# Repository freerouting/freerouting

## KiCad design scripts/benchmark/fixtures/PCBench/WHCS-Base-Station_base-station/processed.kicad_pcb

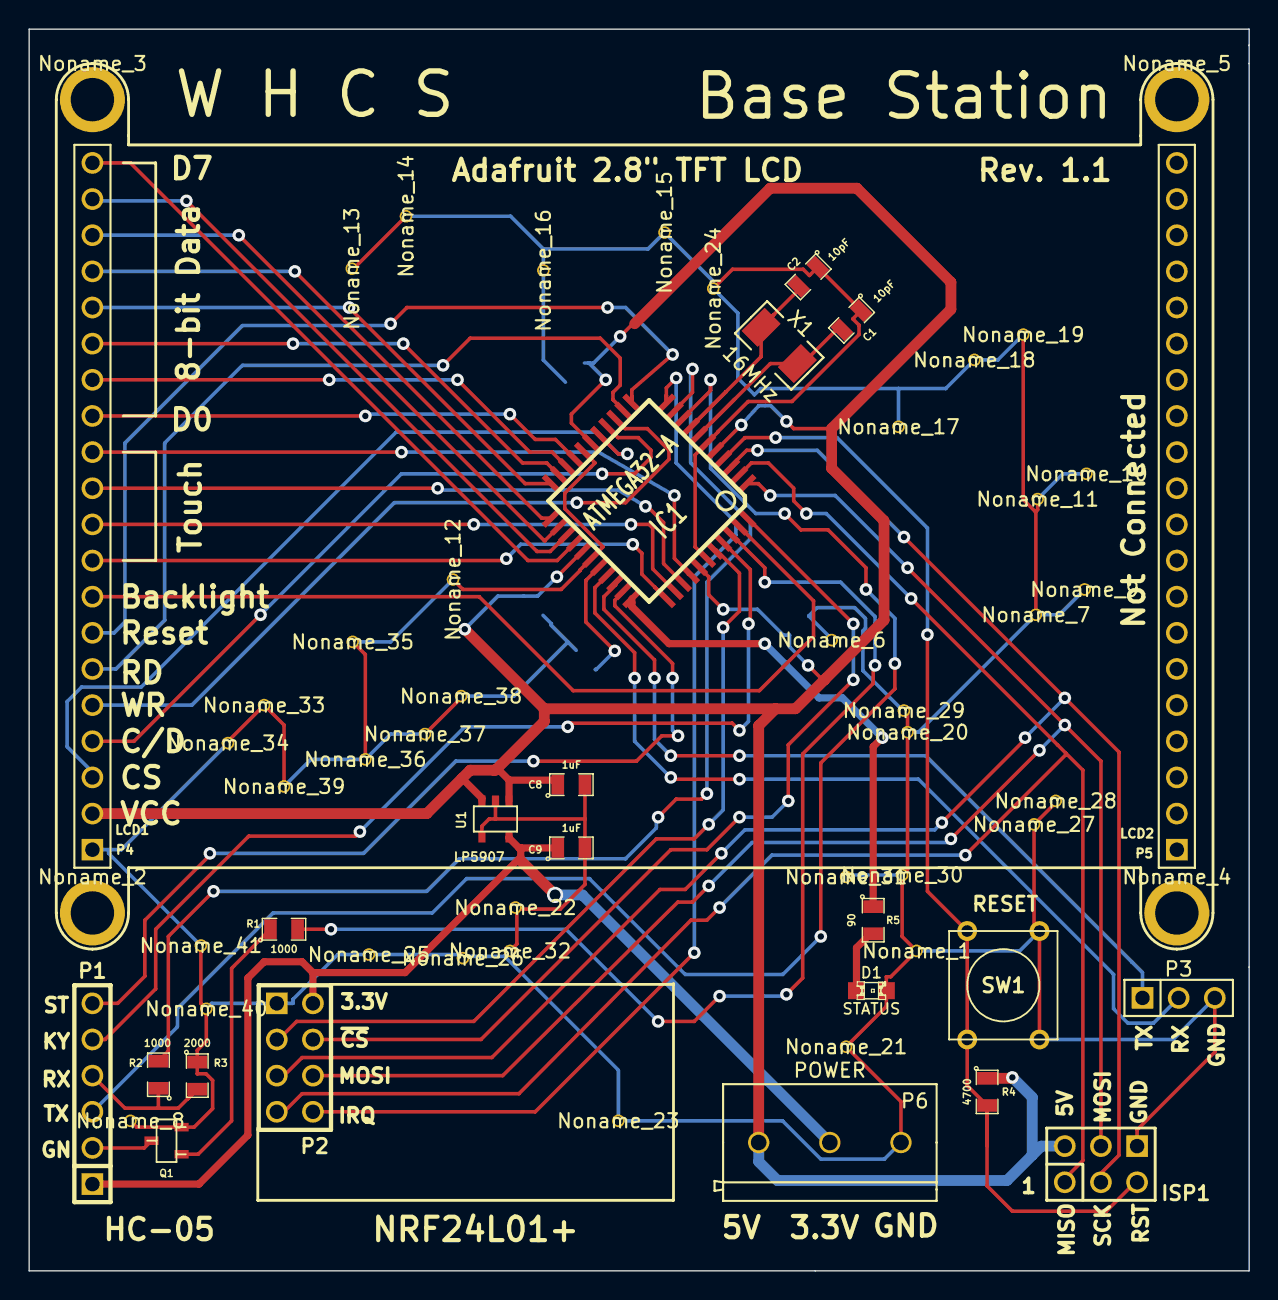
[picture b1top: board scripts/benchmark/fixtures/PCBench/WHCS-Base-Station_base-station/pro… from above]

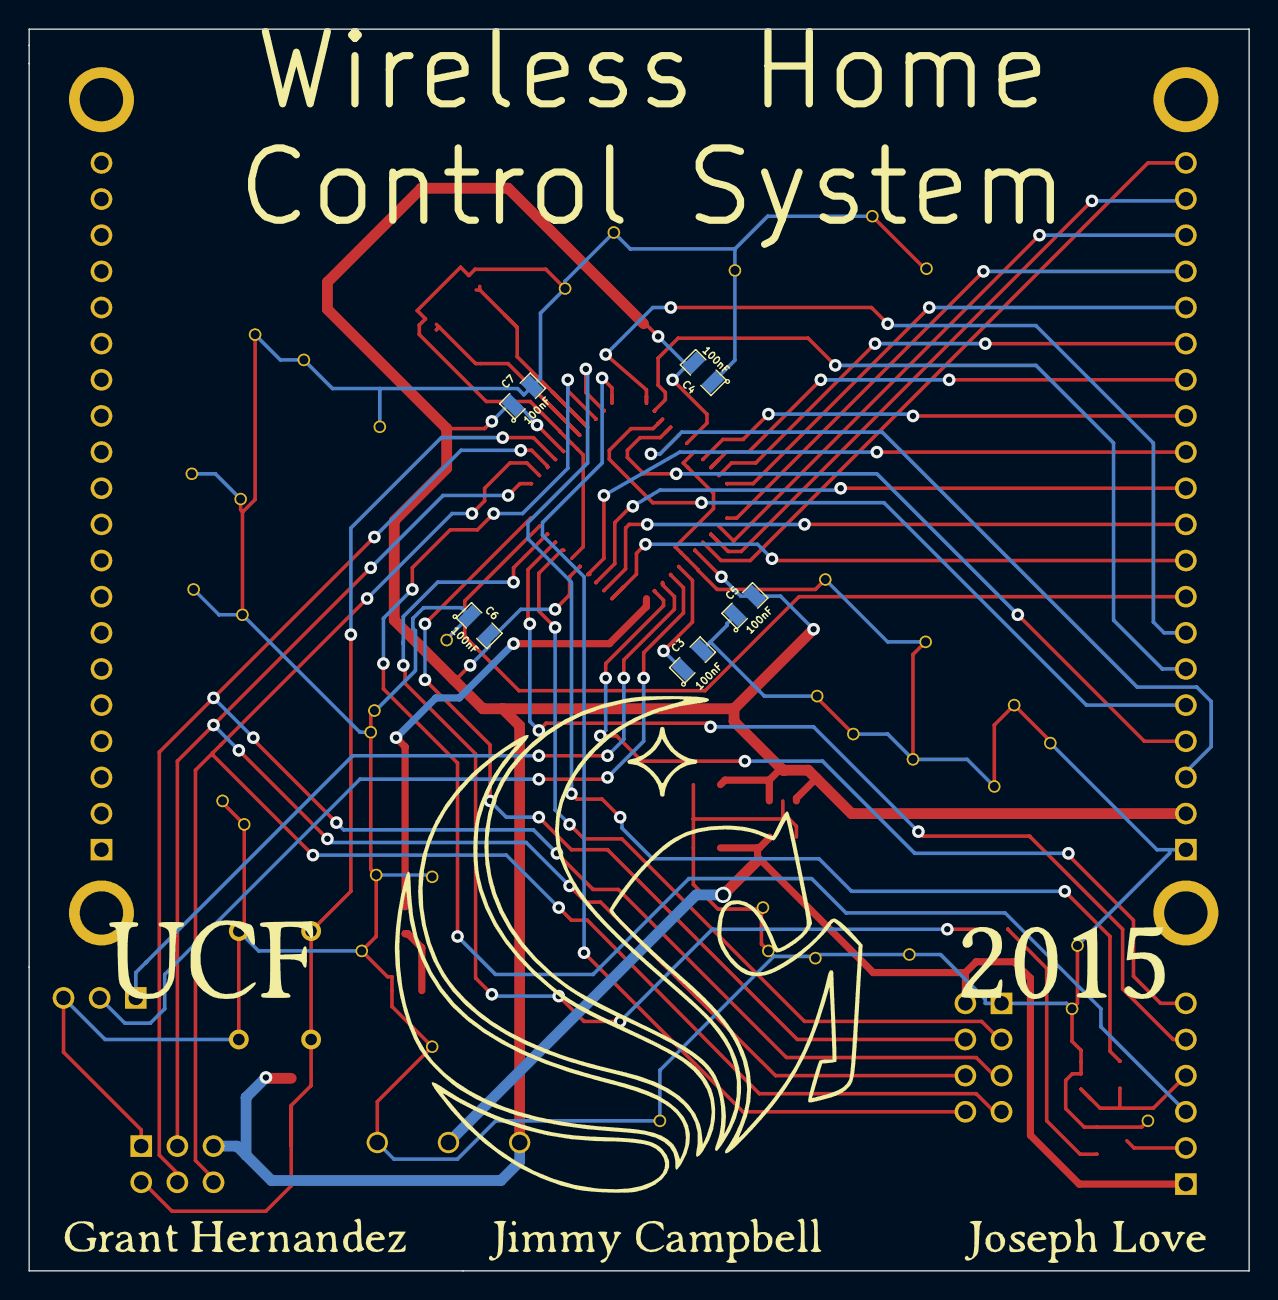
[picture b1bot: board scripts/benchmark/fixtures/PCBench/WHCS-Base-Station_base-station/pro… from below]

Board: 2 copper layers, 85.7 x 87.2 mm, 68 parts (5 on the bottom side), 43 nets.

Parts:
C1, C2: 10pF; SM0805
C3, C4, C5, C6, C7: 100nF; SM0805
C8, C9: 1uF; SM0805
D1: STATUS; LED-0805
IC1: ATMEGA32-A; TQFP44
ISP1: ISP; pin_array_3x2
Noname_1, Noname_6, Noname_7, Noname_8, Noname_9, Noname_10, Noname_11, Noname_12, Noname_13, Noname_14, Noname_15, Noname_16, Noname_17, Noname_18, Noname_19, Noname_20, Noname_21, Noname_22, Noname_23, Noname_24, Noname_25, Noname_26, Noname_27, Noname_28, Noname_29, Noname_30, Noname_31, Noname_32, Noname_33, Noname_34, Noname_35, Noname_36, Noname_37, Noname_38, Noname_39, Noname_40, Noname_41: gnd-via
Noname_2, Noname_3, Noname_4, Noname_5: adafruit-tft-mount
P1: HC-05; PIN_ARRAY-6X1
P2: NRF24L01+; pin_array_4x2
P3: SERIAL; PIN_ARRAY_3X1
P4: LCD1; PIN_ARRAY_20X1
P5: LCD2; PIN_ARRAY_20X1
P6: POWER; terminal-282836-3
Q1: BTEN; sot23
R1, R2: 1000; SM0805
R3: 2000; SM0805
R4: 4700; SM0805
R5: 90; SM0805
SW1: RESET; SW_PUSH_SMALL
U1: LP5907; SOT23-5
X1: 16MHz; 2-SMD

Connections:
/3V3: C9.1, P1.1, P2.2, P6.2, U1.5
/BTEN: IC1.42, R1.2
/CD: IC1.15, P4.4
/CE: IC1.40, P2.3
/CSN: IC1.44, P2.4
/D0: IC1.19, P4.13
/D1: IC1.20, P4.14
/D2: IC1.21, P4.15
/D3: IC1.22, P4.16
/D4: IC1.23, P4.17
/D5: IC1.24, P4.18
/D6: IC1.25, P4.19
/D7: IC1.26, P4.20
/HC_GND: P1.2, Q1.2
/IRQ: IC1.11, P2.8
/KEY: IC1.41, P1.5
/LCS: IC1.16, P4.3
/LITE: IC1.43, P4.8
/LRST: IC1.12, P4.7
/MISO: IC1.2, ISP1.1, P2.7
/MOSI: IC1.1, ISP1.4, P2.6
/PA4: IC1.33, R5.1
/RD: IC1.13, P4.6
/RST: IC1.4, ISP1.5, R4.2, SW1.1
/RX: IC1.9, P1.3
/RX_SOFT: IC1.30, P3.2
/SCK: IC1.3, ISP1.3, P2.5
/STATUS: IC1.32, P1.6
/TX: IC1.10, R2.2
/TX_SOFT: IC1.31, P3.1
/VCC: C4.2, C5.2, C6.2, C7.1, C8.1, IC1.5, IC1.17, IC1.27, IC1.38, ISP1.2, P4.2, P6.1, R4.1, U1.1, U1.3
/WR: IC1.14, P4.5
/X+: IC1.34, P4.9
/X-: IC1.36, P4.11
/Y+: IC1.35, P4.10
/Y-: IC1.37, P4.12
GND: C1.1, C2.1, C3.2, C4.1, C5.1, C6.1, C7.2, C8.2, C9.2, D1.2, IC1.6, IC1.18, IC1.28, IC1.39, ISP1.6, P2.1, P3.3, P4.1, P6.3, Q1.3, R3.1, SW1.2, U1.2, U1.4
unnamed: C1.2, IC1.7, X1.2
unnamed: C2.2, IC1.8, X1.1
unnamed: Q1.1, R1.1
unnamed: P1.4, R2.1, R3.2
unnamed: D1.1, R5.2
unnamed: C3.1, IC1.29

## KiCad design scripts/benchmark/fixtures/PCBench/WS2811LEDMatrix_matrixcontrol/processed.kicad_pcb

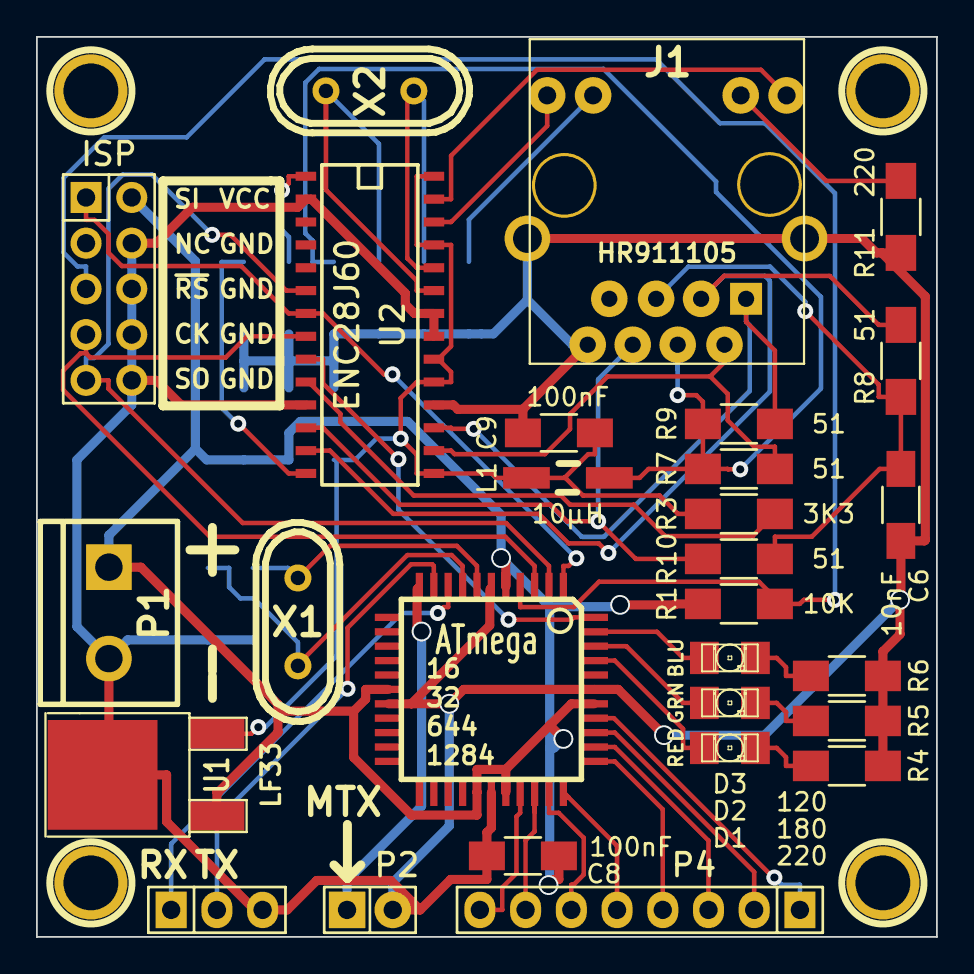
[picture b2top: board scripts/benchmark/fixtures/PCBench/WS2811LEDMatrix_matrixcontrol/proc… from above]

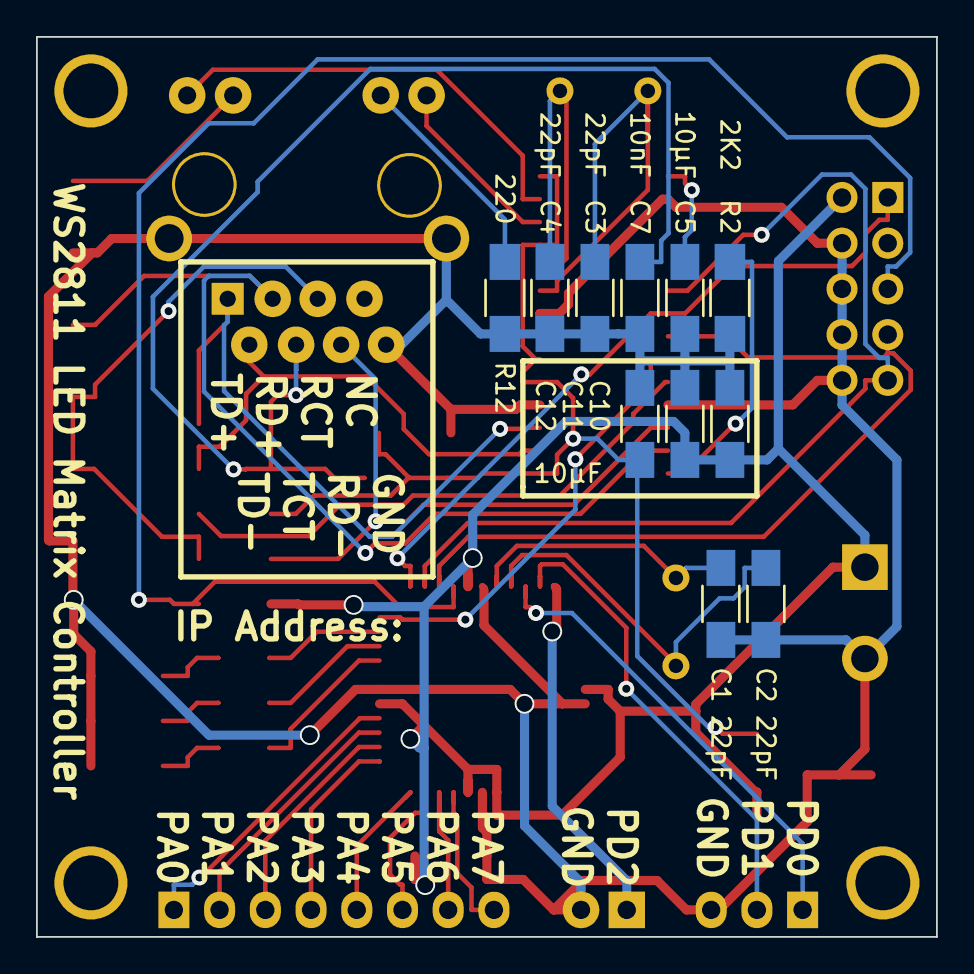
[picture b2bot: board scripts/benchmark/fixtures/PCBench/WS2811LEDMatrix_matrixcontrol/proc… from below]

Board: 2 copper layers, 50.0 x 50.0 mm, 43 parts (11 on the bottom side), 42 nets.

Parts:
C1, C2, C3, C4: 22pF; C_1206_HandSoldering
C5, C10, C11, C12: 10µF; C_1206_HandSoldering
C6, C7: 10nF; C_1206_HandSoldering
C8, C9: 100nF; C_1206_HandSoldering
D1: RED; LED-1206
D2: GRN; LED-1206
D3: BLU; LED-1206
IC1: ATmega; TQFP-44
ISP: ISP; Pin_Header_Straight_2x05
J1: HR911105; HR911105_RJ45
L1: 10µH; Choke_SMD_1206_Handsoldering
MOUNT1, MOUNT2, MOUNT3, MOUNT4: 1pin
P1: POWER_IN; bornier2
P2: MATRIX DATA; Pin_Header_Straight_1x02
P3: SERIAL; Pin_Header_Straight_1x03
P4: CONN_01X08; Pin_Header_Straight_1x08
R1: 10K; R_1206_HandSoldering
R2: 2K2; R_1206_HandSoldering
R3: 3K3; R_1206_HandSoldering
R4, R11, R12: 220; R_1206_HandSoldering
R5: 180; R_1206_HandSoldering
R6: 120; R_1206_HandSoldering
R7, R8, R9, R10: 51; R_1206_HandSoldering
U1: LF33; DPAK-2
U2: ENC28J60; SOIC-28
X1: 16MHz; Crystal_HC49-U_Vertical
X2: 25MHz; Crystal_HC49-U_Vertical

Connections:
+5V: C8.1, C10.1, C11.1, IC1.5, IC1.17, IC1.27, IC1.29, IC1.38, ISP.2, P1.1, R1.1, U1.1
/MISO: IC1.2, ISP.9, U2.6
/MOSI: IC1.1, ISP.1, U2.7
/MTX_DAT: IC1.11, P2.1
/RXD: IC1.9, P3.1
/SCK: IC1.3, ISP.7, U2.8
/STATLED1: D1.1, IC1.41
/STATLED2: D2.1, IC1.42
/STATLED3: D3.1, IC1.43
/TXD: IC1.10, P3.2
/~RESET: IC1.4, ISP.5, R1.2
GND: C1.2, C2.2, C3.2, C4.2, C5.2, C6.2, C7.2, C8.2, C9.2, C10.2, C11.2, C12.2, IC1.6, IC1.18, IC1.28, IC1.39, ISP.4, ISP.6, ISP.8, ISP.10, J1.0, J1.8, P1.2, P2.2, P3.3, R2.2, R4.1, R5.1, R6.1, R11.2, R12.2, U1.2, U2.2, U2.11, U2.18, U2.21, U2.22
unnamed: C1.1, IC1.7, X1.1
unnamed: C2.1, IC1.8, X1.2
unnamed: C3.1, U2.23, X2.1
unnamed: C4.1, U2.24, X2.2
unnamed: C5.1, U2.1
unnamed: C6.1, J1.5, R8.2, R10.2
unnamed: C7.1, J1.4, L1.2, R7.1, R9.1
unnamed: C9.1, C12.1, L1.1, R3.1, U1.3, U2.15, U2.19, U2.20, U2.25, U2.28
unnamed: D1.2, R4.2
unnamed: D2.2, R5.2
unnamed: D3.2, R6.2
unnamed: IC1.30, P4.8
unnamed: IC1.31, P4.7
unnamed: IC1.32, P4.6
unnamed: IC1.33, P4.5
unnamed: IC1.34, P4.4
unnamed: IC1.35, P4.3
unnamed: IC1.36, P4.2
unnamed: IC1.37, P4.1
unnamed: IC1.44, U2.9
unnamed: J1.1, R9.2, U2.17
unnamed: J1.2, R7.2, U2.16
unnamed: J1.3, R8.1, U2.13
unnamed: J1.6, R10.1, U2.12
unnamed: J1.9, U2.27
unnamed: J1.10, R11.1
unnamed: J1.11, R12.1
unnamed: J1.12, U2.26
unnamed: R2.1, U2.14
unnamed: R3.2, U2.10

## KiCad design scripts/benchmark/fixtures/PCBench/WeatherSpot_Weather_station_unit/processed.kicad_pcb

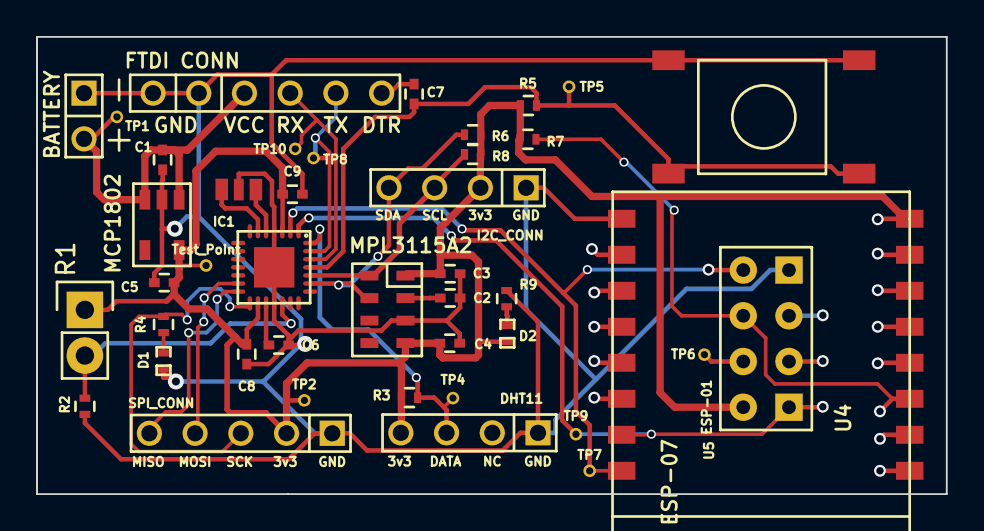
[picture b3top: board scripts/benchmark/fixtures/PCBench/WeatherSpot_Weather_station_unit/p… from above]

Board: 2 copper layers, 50.5 x 25.4 mm, 42 parts (0 on the bottom side), 24 nets.

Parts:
BT1: BATTERY; BATT_CONN
C1, C5: 1uF; C_0402
C2, C4: 100nF; C_0402
C3: 10uF; C_0402
C6, C7, C8, C9: 0.1uF; C_0402
D1, D2: LED; SMD-0402_LED
IC1: ATMEGA328P-MM; QFN-28-4x4mm_fixed_mask
P1: FTDI CONN; FTDI_PORT
Q1: Oscilator; ceramic_resonator_smd
R1: PhotoResistor; Socket_Strip_Straight_1x02
R2, R5, R7: 10K; R_0402
R3: 5K; R_0402
R4, R9: 470; R_0402
R6, R8: 4.7K; R_0402
SW1: SW_PUSH; push_switch_SMD
TP1: TP1; TEST_POINT
TP2: TP2; TEST_POINT
TP3: Test_Point; TEST_POINT
TP4: TP4; TEST_POINT
TP5: TP5; TEST_POINT
TP6: TP6; TEST_POINT
TP7: TP7; TEST_POINT
TP8: TP8; TEST_POINT
TP9: TP9; TEST_POINT
TP10: TP10; TEST_POINT
U1: MPL3115A2
U2: MCP1802; MCP1802T
U3: DHT11
U4: ESP-07
U5: ESP-01
conn1: I2C_CONN
conn2: SPI_CONN

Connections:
3V3: C3.1, C4.1, C5.1, C8.1, C9.1, D2.2, IC1.3, IC1.16, R1.1, R3.1, R5.1, R6.1, R7.1, R8.1, TP2.1, TP3.1, U1.1, U1.4, U2.5, U3.1, U4.8, U5.4, conn1.3, conn2.4
/D2: IC1.28, R3.2, TP4.1, U3.2
/DTR: C7.1, P1.6
/MISO: IC1.14, conn2.1
/MOSI: IC1.13, conn2.2
/RX: IC1.26, P1.4, TP10.1
/RXS: IC1.1, TP9.1, U4.15, U5.5
/SCK: IC1.15, R4.2, conn2.3
/TX: IC1.27, P1.5, TP8.1
/TXS: IC1.2, TP7.1, U4.16, U5.1
/VCC: BT1.1, C1.1, P1.3, TP1.1, U2.1, U2.3
A0: IC1.19, R1.2, R2.1
GND: BT1.2, C1.2, C2.2, C3.2, C4.2, C5.2, C6.2, C8.2, C9.2, D1.2, IC1.4, IC1.18, P1.1, P1.2, Q1.1, R2.2, R9.2, SW1.2, U1.3, U2.2, U3.4, U4.9, U5.8, conn1.4, conn2.5
unnamed: C2.1, U1.2
unnamed: C6.1, IC1.17
unnamed: C7.2, IC1.25, R5.2, SW1.1, TP5.1
unnamed: D1.1, R4.1
unnamed: D2.1, R9.1
unnamed: IC1.5, Q1.3
unnamed: IC1.6, Q1.2
unnamed: R7.2, U4.3, U5.2
unnamed: TP6.1, U5.3
SCL: IC1.24, R8.2, U1.8, conn1.2
SDA: IC1.23, R6.2, U1.7, conn1.1
